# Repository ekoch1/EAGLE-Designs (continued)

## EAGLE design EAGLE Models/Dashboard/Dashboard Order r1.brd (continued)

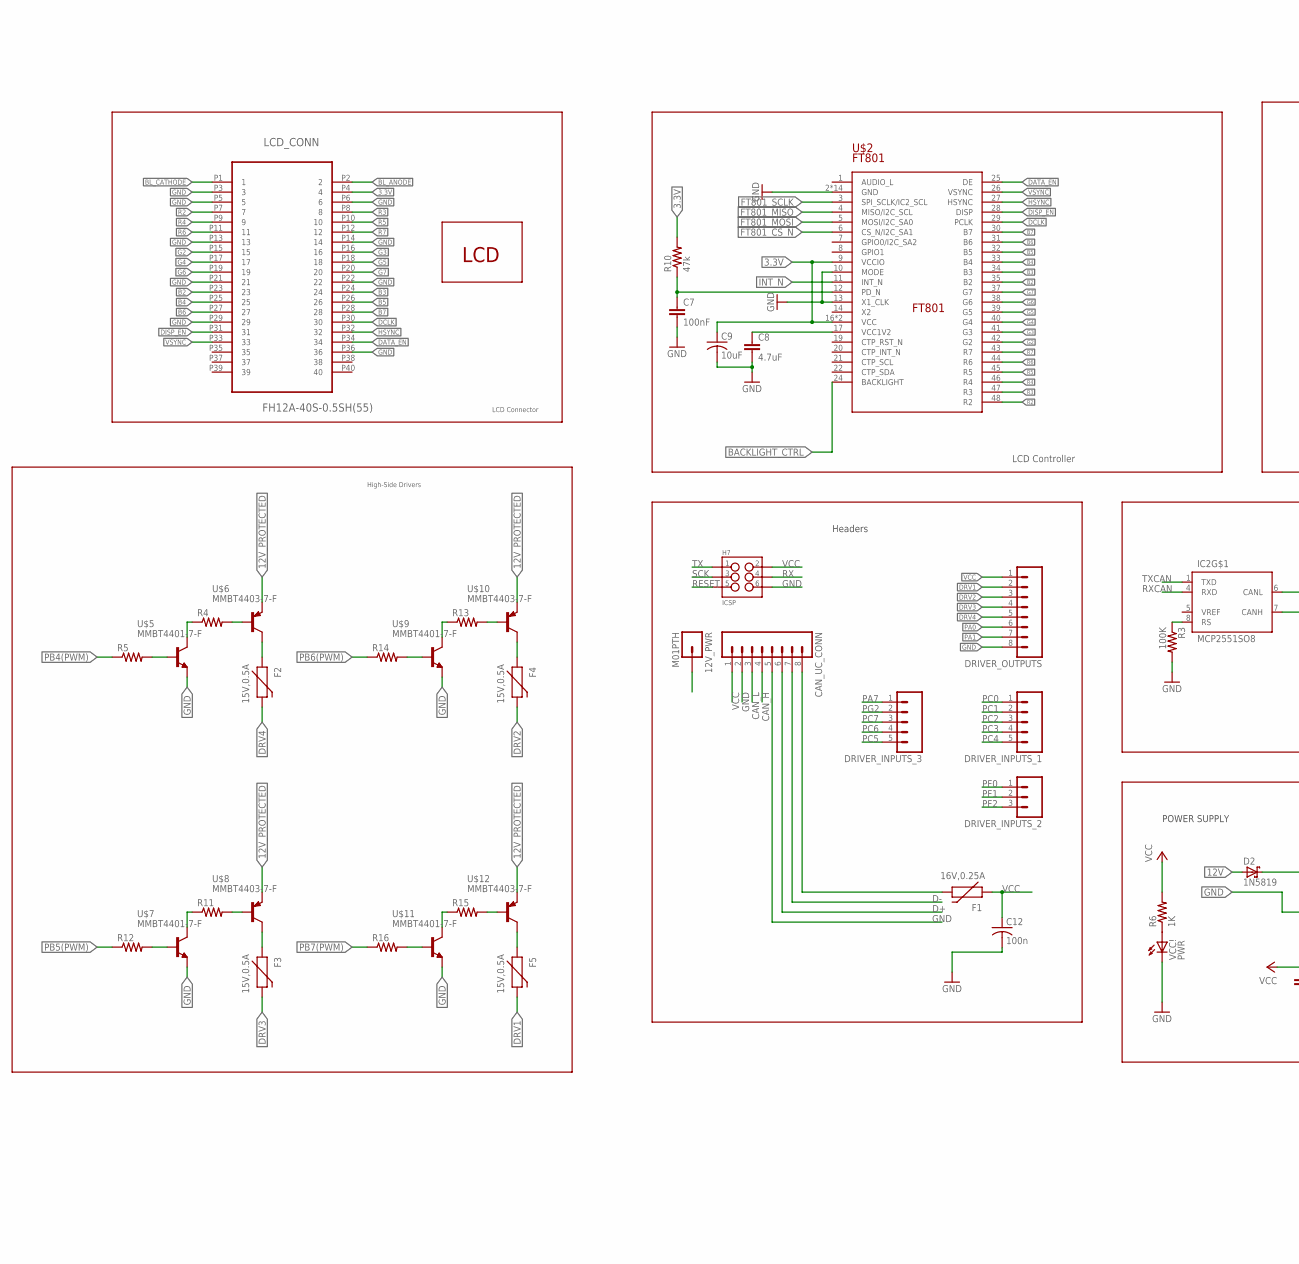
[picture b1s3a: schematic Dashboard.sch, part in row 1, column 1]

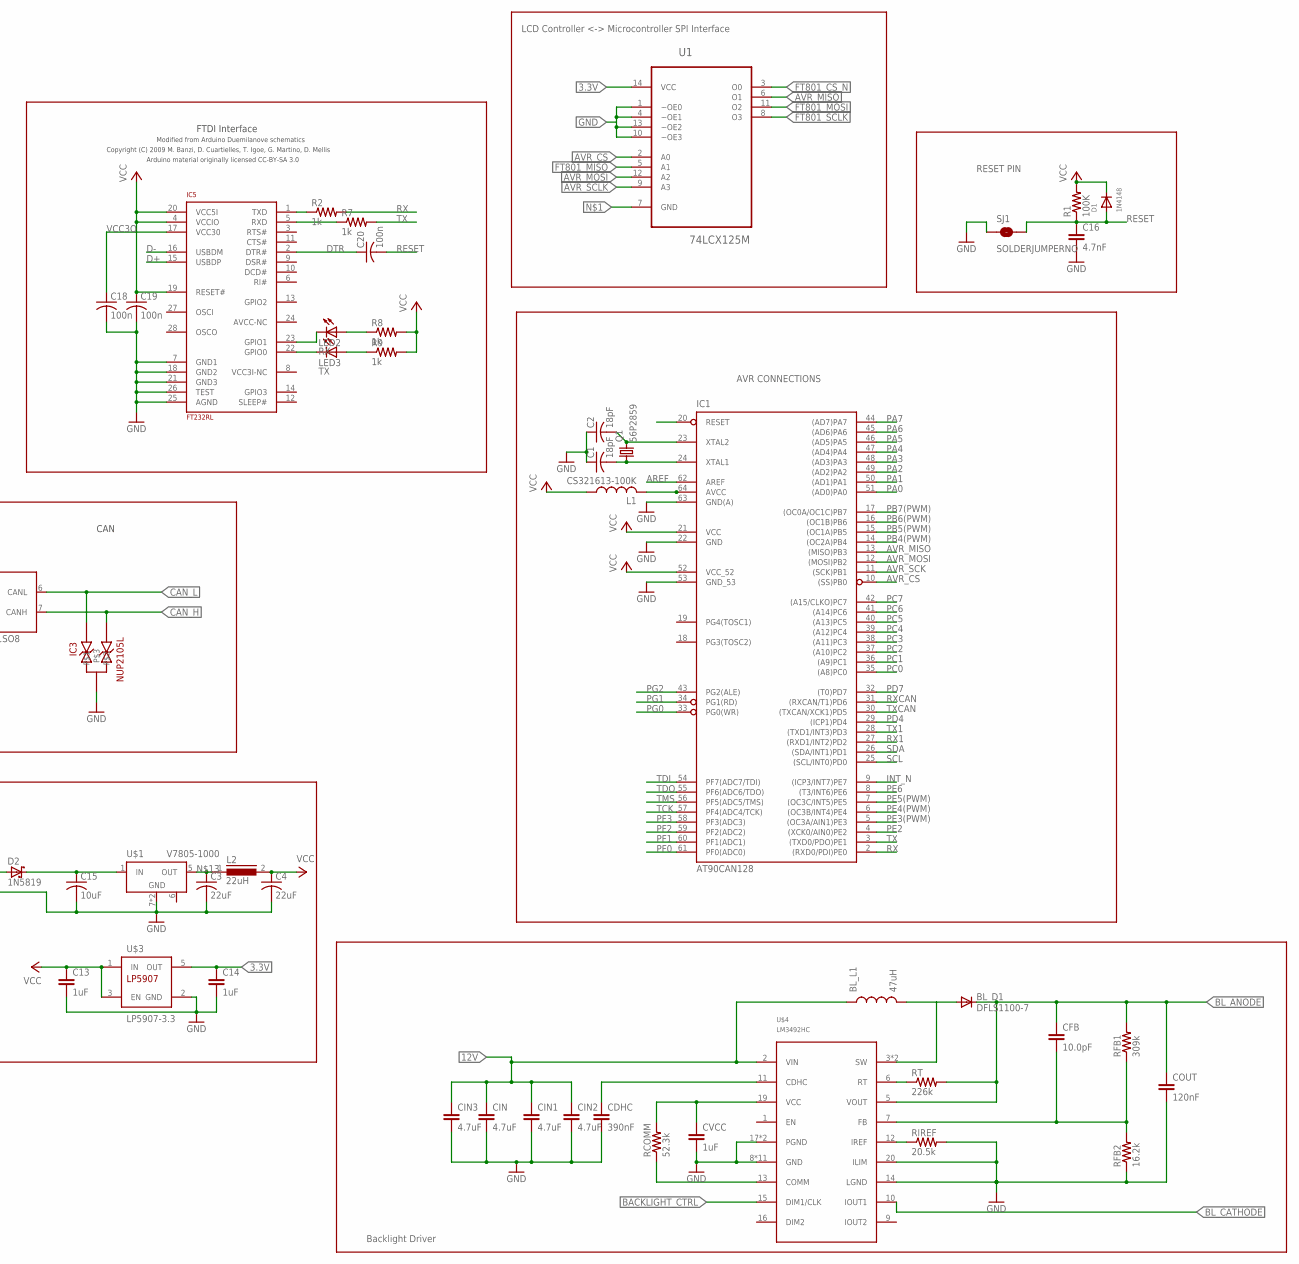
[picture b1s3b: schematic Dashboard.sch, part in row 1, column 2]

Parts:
12V_PWR: M01PTH; 1X01
BL_D1: DFLS1100-7; POWERDI-123
BL_L1: 47uH; 2-SMD
C1, C2: 18pF; C0805
C3, C4: 22uF; C2220
C7: 100nF; 0603-CAP
C8: 4.7uF; 0805
C9, C15: 10uF; C2220
C12, C18, C19, C20: 100n; C0805
C13, C14: 1uF; 0603-CAP
C16: 4.7nF; 0805
CAN_UC_CONN: M081X08; 1X08
CDHC: 390nF; 0603-CAP
CFB: 10.0pF; 0603-CAP
CIN, CIN1, CIN2, CIN3: 4.7uF; 0805
COUT: 120nF; 0805
CVCC: 1uF; 0603-CAP
D1: 1N4148; SOD-123
D2: 1N5819; SOD123
DRIVER_INPUTS_1, DRIVER_INPUTS_3: M05PTH; 1X05
DRIVER_INPUTS_2: M03PTH; 1X03
DRIVER_OUTPUTS: M081X08; 1X08
F1: 16V,0.25A; PTC-1206
F2, F3, F4, F5: 15V,0.5A; PTC-1206
H7: ICSP; 2X3_SMD_FCI_54202-G30
IC1: AT90CAN128; TQFP64
IC2: MCP2551SO8; SO08
IC3: NUP2105L; SOT-23
IC5: FT232RL; SSOP28
L1: CS321613-100K; L3216C
L2: 22uH; DR73
LCD_CONN: FH12A-40S-0.5SH(55); HIROSE_FH12A-40S-0.5SH(55)
LED2: RX; CHIPLED_0805
LED3: TX; CHIPLED_0805
Q1: 56P2859; HC49UP
R1, R3: 100K; R0805
R2, R7, R8, R9: 1k; R0805
R4, R5, R11, R12, R13, R14, R15, R16: RESISTOR0603; 0603-RES
R6: 1K; R0805
R10: 47k; 0603-RES
RCOMM: 52.3k; 0603-RES
RFB1: 309k; 0603-RES
RFB2: 16.2k; 0603-RES
RIREF: 20.5k; 0603-RES
RT: 226k; 0603-RES
SJ1: SOLDERJUMPERNO; SJ_2S-NO
U1: 74LCX125M; SOIC127P600X175-14N
U$1: V7805-1000; V78XX-1000
U$2: FT801; RGZ48_5P15X5P15
U$3: LP5907-3.3; SOT23-DBV
U$4: LM3492HC; PWP0020A
U$5, U$7, U$9, U$11: MMBT4401-7-F; SOT-23-3
U$6, U$8, U$10, U$12: MMBT4403-7-F; SOT-23-3
U$13: TCG043WQLBAANN-GN00; TCG043WQLBAANN
VCC!: PWR; CHIPLED_0805

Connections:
3.3V: C9.1, C14.1, LCD_CONN.P4 (4), R10.2, U1.14 (VCC), U$2.9 (VCCIO), U$2.16 (VCC), U$2.18 (VCC), U$3.5 (OUT)
12V: 12V_PWR.1, BL_L1.1, CIN.1, CIN1.1, CIN2.1, CIN3.1, D2.A, U$4.2 (VIN); also elsewhere on the board
12V_PROTECTED: C15.1, D2.C, U$1.1 (IN), U$6.P$3 (E), U$8.P$3 (E), U$10.P$3 (E), U$12.P$3 (E)
AREF: IC1.62 (AREF)
AVR_CS: IC1.10 ((SS)PB0), U1.2 (A0)
AVR_MISO: IC1.13 ((MISO)PB3), U1.6 (O1)
AVR_MOSI: IC1.12 ((MOSI)PB2), U1.12 (A2)
B2: LCD_CONN.P23 (23), U$2.35 (B2)
B3: LCD_CONN.P24 (24), U$2.34 (B3)
B4: LCD_CONN.P25 (25), U$2.33 (B4)
B5: LCD_CONN.P26 (26), U$2.32 (B5)
B6: LCD_CONN.P27 (27), U$2.31 (B6)
B7: LCD_CONN.P28 (28), U$2.30 (B7)
BACKLIGHT_CTRL: U$2.24 (BACKLIGHT), U$4.15 (DIM1/CLK)
BL_ANODE: BL_D1.C, CFB.1, COUT.1, LCD_CONN.P2 (2), RFB1.2, RT.2, U$4.5 (VOUT)
BL_CATHODE: LCD_CONN.P1 (1), U$4.10 (IOUT1)
CAN_H: CAN_UC_CONN.4, IC2.7 (CANH), IC3.2; also elsewhere on the board
CAN_L: CAN_UC_CONN.3, IC2.6 (CANL), IC3.1; also elsewhere on the board
D+: CAN_UC_CONN.6, IC5.15 (USBDP); also elsewhere on the board
D-: CAN_UC_CONN.7, IC5.16 (USBDM); also elsewhere on the board
DATA_EN: LCD_CONN.P34 (34), U$2.25 (DE)
DCLK: LCD_CONN.P30 (30), U$2.29 (PCLK)
DISP_EN: LCD_CONN.P31 (31), U$2.28 (DISP)
DRV1: DRIVER_OUTPUTS.2, F5.2; also elsewhere on the board
DRV2: DRIVER_OUTPUTS.3, F4.2; also elsewhere on the board
DRV3: DRIVER_OUTPUTS.4, F3.2; also elsewhere on the board
DRV4: DRIVER_OUTPUTS.5, F2.2
DTR: C20.1, IC5.2 (DTR#)
FT801_CS_N: U1.3 (O0), U$2.6 (CS_N/I2C_SA1)
FT801_MISO: U1.5 (A1), U$2.4 (MISO/I2C_SCL)
FT801_MOSI: U1.11 (O2), U$2.5 (MOSI/I2C_SA0)
FT801_SCLK: U1.8 (O3), U$2.3 (SPI_SCLK/IC2_SCL)
G2: LCD_CONN.P15 (15), U$2.42 (G2)
G3: LCD_CONN.P16 (16), U$2.41 (G3)
G4: LCD_CONN.P17 (17), U$2.40 (G4)
G5: LCD_CONN.P18 (18), U$2.39 (G5)
G6: LCD_CONN.P19 (19), U$2.38 (G6)
G7: LCD_CONN.P20 (20), U$2.37 (G7)
GND: C1.1, C2.1, C3.2, C4.2, C7.2, C8.2, C9.2, C12.2, C13.2, C14.2, C15.2, C16.2, C18.2, C19.2, CAN_UC_CONN.2, CAN_UC_CONN.5, CDHC.2, CIN.2, CIN1.2, CIN2.2, CIN3.2, COUT.2, CVCC.2, DRIVER_OUTPUTS.8, H7.6, IC1.22 (GND), IC1.53 (GND_53), IC1.63 (GND(A)), IC2.2 (GND), IC3.3, IC5.7 (GND1), IC5.18 (GND2), IC5.21 (GND3), IC5.25 (AGND), IC5.26 (TEST), LCD_CONN.P3 (3), LCD_CONN.P5 (5), LCD_CONN.P6 (6), LCD_CONN.P13 (13), LCD_CONN.P14 (14), LCD_CONN.P21 (21), LCD_CONN.P22 (22), LCD_CONN.P29 (29), LCD_CONN.P36 (36), R3.2, RFB2.1, RIREF.2, SJ1.1, U1.1 (~OE0), U1.4 (~OE1), U1.10 (~OE3), U1.13 (~OE2), U$1.7 (GND), U$1.9 (GND), U$2.2 (GND), U$2.10 (MODE), U$2.13 (X1_CLK), U$2.15 (GND), U$2.23 (GND), U$2.36 (GND), U$2.EP (GND), U$2.V_1 (GND), U$2.V_2 (GND), U$2.V_3 (GND), U$2.V_4 (GND), U$2.V_5 (GND), U$2.V_6 (GND), U$2.V_7 (GND), U$2.V_8 (GND), U$2.V_9 (GND), U$3.2 (GND), U$4.8 (GND), U$4.14 (LGND), U$4.17 (PGND), U$4.18 (PGND), U$4.20 (ILIM), U$4.EP (GND), U$4.P$1 (GND), U$4.P$2 (GND), U$4.P$3 (GND), U$4.P$4 (GND), U$4.P$5 (GND), U$4.P$6 (GND), U$4.P$7 (GND), U$4.P$8 (GND), U$4.P$9 (GND), U$5.P$3 (E), U$7.P$3 (E), U$9.P$3 (E), U$11.P$3 (E), VCC!.C; also elsewhere on the board
HSYNC: LCD_CONN.P32 (32), U$2.27 (HSYNC)
INT_N: IC1.9 ((ICP3/INT7)PE7), U$2.11 (INT_N)
M8RXD: IC5.1 (TXD), R2.1
M8TXD: IC5.5 (RXD), R7.1
unnamed: C8.1, U$2.17 (VCC1V2)
unnamed: C7.1, R10.1, U$2.12 (PD_N)
unnamed: CVCC.1, RCOMM.2, U$4.19 (VCC)
unnamed: RCOMM.1, U$4.13 (COMM)
unnamed: IC2.8 (RS), R3.1
unnamed: CDHC.1, U$4.11 (CDHC)
unnamed: BL_D1.A, BL_L1.2, U$4.3 (SW), U$4.4 (SW)
unnamed: R6.1, VCC!.A
unnamed: CFB.2, RFB1.1, RFB2.2, U$4.7 (FB)
unnamed: C1.2, IC1.24 (XTAL1), Q1.1
unnamed: RT.1, U$4.6 (RT)
unnamed: C3.1, L2.1, U$1.5 (OUT)
unnamed: RIREF.1, U$4.12 (IREF)
unnamed: IC1.64 (AVCC), L1.2
unnamed: R5.2, U$5.P$2 (B)
unnamed: R4.2, U$6.P$2 (B)
unnamed: R4.1, U$5.P$1 (C)
unnamed: F2.1, U$6.P$1 (C)
unnamed: R12.2, U$7.P$2 (B)
unnamed: R11.2, U$8.P$2 (B)
unnamed: R11.1, U$7.P$1 (C)
unnamed: F3.1, U$8.P$1 (C)
unnamed: R14.2, U$9.P$2 (B)
unnamed: IC5.23 (GPIO1), LED2.C
unnamed: R13.2, U$10.P$2 (B)
unnamed: IC5.22 (GPIO0), LED3.C
unnamed: LED2.A, R8.1
unnamed: LED3.A, R9.1
unnamed: R13.1, U$9.P$1 (C)
unnamed: F4.1, U$10.P$1 (C)
unnamed: R16.2, U$11.P$2 (B)
unnamed: R15.2, U$12.P$2 (B)
unnamed: R15.1, U$11.P$1 (C)
unnamed: F5.1, U$12.P$1 (C)
PA0: DRIVER_OUTPUTS.6, IC1.51 ((AD0)PA0)
PA1: DRIVER_OUTPUTS.7, IC1.50 ((AD1)PA1)
PA2: IC1.49 ((AD2)PA2)
PA3: IC1.48 ((AD3)PA3)
PA4: IC1.47 ((AD4)PA4)
PA5: IC1.46 ((AD5)PA5)
PA6: IC1.45 ((AD6)PA6)
PA7: DRIVER_INPUTS_3.1, IC1.44 ((AD7)PA7)
PB4(PWM): IC1.14 ((OC2A)PB4), R5.1
PB5(PWM): IC1.15 ((OC1A)PB5), R12.1
PB6(PWM): IC1.16 ((OC1B)PB6), R14.1
PB7(PWM): IC1.17 ((OC0A/OC1C)PB7), R16.1
PC0: DRIVER_INPUTS_1.1, IC1.35 ((A8)PC0); also elsewhere on the board
PC1: DRIVER_INPUTS_1.2, IC1.36 ((A9)PC1)
PC2: DRIVER_INPUTS_1.3, IC1.37 ((A10)PC2)
PC3: DRIVER_INPUTS_1.4, IC1.38 ((A11)PC3)
PC4: DRIVER_INPUTS_1.5, IC1.39 ((A12)PC4)
PC5: DRIVER_INPUTS_3.5, IC1.40 ((A13)PC5)
PC6: DRIVER_INPUTS_3.4, IC1.41 ((A14)PC6)
PC7: DRIVER_INPUTS_3.3, IC1.42 ((A15/CLKO)PC7)
PD4: IC1.29 ((ICP1)PD4)
PD7: IC1.32 ((T0)PD7)
PE2: IC1.4 ((XCK0/AIN0)PE2)
PE3(PWM): IC1.5 ((OC3A/AIN1)PE3)
PE4(PWM): IC1.6 ((OC3B/INT4)PE4)
PE5(PWM): IC1.7 ((OC3C/INT5)PE5)
PE6: IC1.8 ((T3/INT6)PE6)
PF0: DRIVER_INPUTS_2.1, IC1.61 (PF0(ADC0)); also elsewhere on the board
PF1: DRIVER_INPUTS_2.2, IC1.60 (PF1(ADC1)); also elsewhere on the board
PF2: DRIVER_INPUTS_2.3, IC1.59 (PF2(ADC2)); also elsewhere on the board
PF3: IC1.58 (PF3(ADC3))
PG0: IC1.33 (PG0(WR))
PG1: IC1.34 (PG1(RD))
PG2: DRIVER_INPUTS_3.2, IC1.43 (PG2(ALE))
R2: LCD_CONN.P7 (7), U$2.48 (R2)
R3: LCD_CONN.P8 (8), U$2.47 (R3)
R4: LCD_CONN.P9 (9), U$2.46 (R4)
R5: LCD_CONN.P10 (10), U$2.45 (R5)
R6: LCD_CONN.P11 (11), U$2.44 (R6)
R7: LCD_CONN.P12 (12), U$2.43 (R7)
RESET: C16.1, C20.2, D1.A, H7.5, IC1.20 (RESET), R1.1, SJ1.2
RX: H7.4, IC1.2 ((RXD0/PDI)PE0), R2.2
RX1: IC1.27 ((RXD1/INT2)PD2)
RXCAN: IC1.31 ((RXCAN/T1)PD6), IC2.4 (RXD)
SCK: H7.3
SCL: IC1.25 ((SCL/INT0)PD0)
SDA: IC1.26 ((SDA/INT1)PD1)
TCK: IC1.57 (PF4(ADC4/TCK))
TDI: IC1.54 (PF7(ADC7/TDI))
TDO: IC1.55 (PF6(ADC6/TDO))
TMS: IC1.56 (PF5(ADC5/TMS))
TX: H7.1, IC1.3 ((TXD0/PDO)PE1), R7.2
TX1: IC1.28 ((TXD1/INT3)PD3)
TXCAN: IC1.30 ((TXCAN/XCK1)PD5), IC2.1 (TXD)
USB_V_IN: CAN_UC_CONN.8, F1.2; also elsewhere on the board
VCC: C4.1, C12.1, C13.1, C19.1, CAN_UC_CONN.1, D1.C, DRIVER_OUTPUTS.1, F1.1, H7.2, IC1.21 (VCC), IC1.52 (VCC_52), IC2.3 (VCC), IC5.4 (VCCIO), IC5.19 (RESET#), IC5.20 (VCC5I), L1.1, L2.2, R1.2, R6.2, R8.2, R9.2, U$3.1 (IN), U$3.3 (EN); also elsewhere on the board
VCC3O: C18.1, IC5.17 (VCC30)
VSYNC: LCD_CONN.P33 (33), U$2.26 (VSYNC)
XTAL1: C2.2, IC1.23 (XTAL2), Q1.2

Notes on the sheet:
POWER SUPPLY
CAN
RESET PIN
AVR CONNECTIONS
FTDI Interface
Headers
Modified from Arduino Duemilanove schematics
Copyright (C) 2009 M. Banzi, D. Cuartielles, T. Igoe, G. Martino, D. Mellis
Arduino material originally licensed CC-BY-SA 3.0
LCD Controller
LCD Controller <-> Microcontroller SPI Interface
Backlight Driver
LCD Connector
High-Side Drivers

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
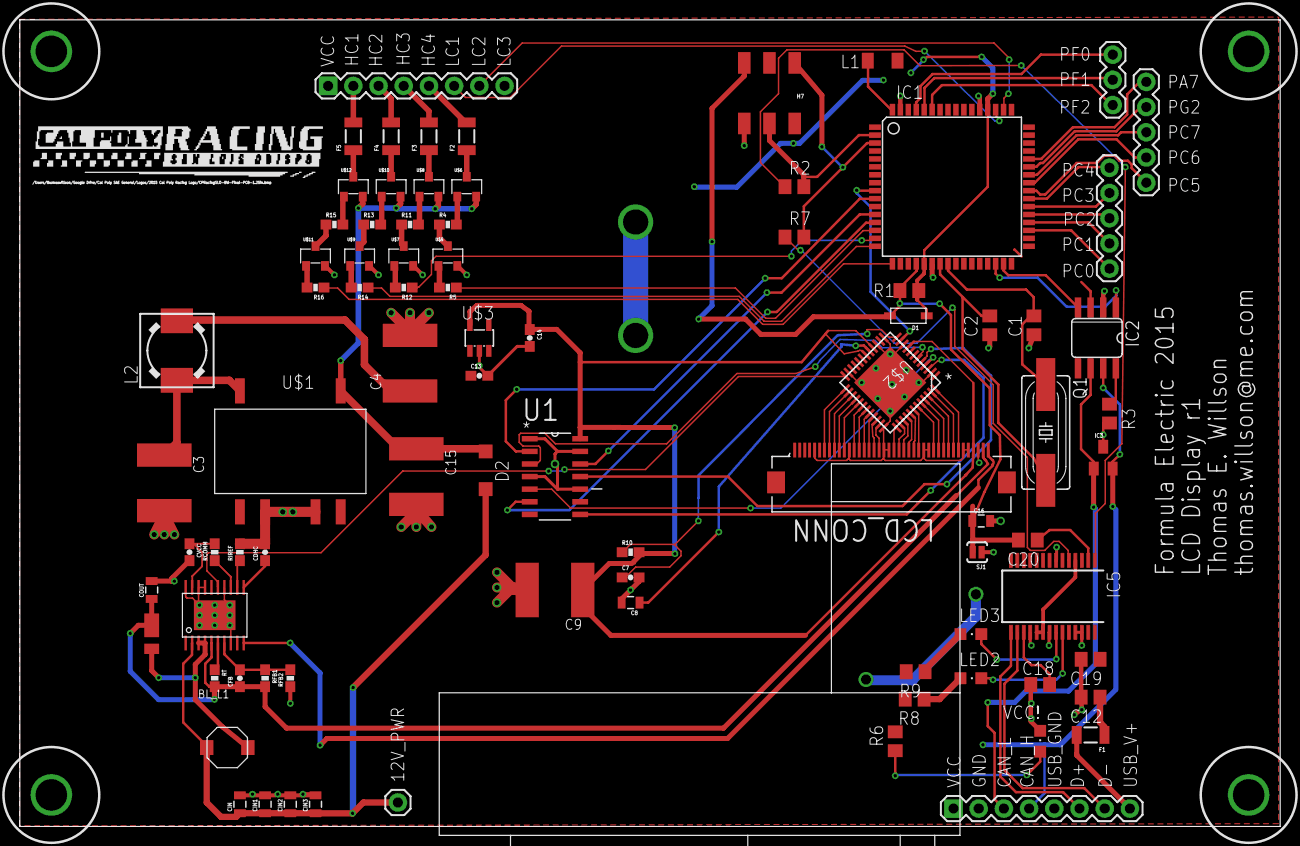
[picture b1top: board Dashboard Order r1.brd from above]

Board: 2 copper layers, 127.0 x 81.3 mm, 86 parts (0 on the bottom side), 111 nets.

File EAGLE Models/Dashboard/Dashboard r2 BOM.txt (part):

Partlist exported from C:/Users/Daniel Baron/Desktop/FSAE2016Boards and Schematics/Dashboard12-12.sch at 1/12/2016 12:52 PM

Part     Value               Device              Package                    Description                                                                         MPN                 OC_FARNELL OC_NEWARK PACKAGE                           SUPPLIER 
BL_D1    DFLS1100-7          DFLS1100-7          POWERDI-123                                                                                                                                                                                        
BL_L1    47uH                LTF4022-D           2-SMD                      LTF4022                                                                                                                                                                 
C1       18pF                C-USC0805           C0805                      CAPACITOR, American symbol                                                                                                                                              
C2       18pF                C-USC0805           C0805                      CAPACITOR, American symbol                                                                                                                                              
C3       22uF                C-USC2220           C2220                      CAPACITOR, American symbol                                                                                                                                              
C4       22uF                C-USC2220           C2220                      CAPACITOR, American symbol                                                                                                                                              
C7       100nF               CAP0603-CAP         0603-CAP                   Capacitor                                                                                                                                                               
C8       4.7uF               CAP0805             0805                       Capacitor                                                                                                                                                               
C9       10uF                C-USC2220           C2220                      CAPACITOR, American symbol                                                                                                                                              
C12      100n                C-USC0805           C0805                      CAPACITOR, American symbol                                                                                                                                              
C13      1uF                 CAP0603-CAP         0603-CAP                   Capacitor                                                                                                                                                               
C14      1uF                 CAP0603-CAP         0603-CAP                   Capacitor                                                                                                                                                               
C15      10uF                C-USC2220           C2220                      CAPACITOR, American symbol                                                                                                                                              
C16      4.7nF               CAP0805             0805                       Capacitor                                                                                                                                                               
C18      100n                C-USC0805           C0805                      CAPACITOR, American symbol                                                                                                                                              
C19      100n                C-USC0805           C0805                      CAPACITOR, American symbol                                                                                                                                              
C20      100n                C-USC0805           C0805                      CAPACITOR, American symbol                                                                                                                                              
CANPWR   MICRO5LOCK          MICRO5LOCK          MICRO5LOCK                                                                                                                                                                                         
CDHC     390nF               CAP0603-CAP         0603-CAP                   Capacitor                                                                                                                                                               
CFB      10.0pF              CAP0603-CAP         0603-CAP                   Capacitor                                                                                                                                                               
CIN      4.7uF               CAP0805             0805                       Capacitor                                                                                                                                                               
CIN1     4.7uF               CAP0805             0805                       Capacitor                                                                                                                                                               
CIN2     4.7uF               CAP0805             0805                       Capacitor                                                                                                                                                               
CIN3     4.7uF               CAP0805             0805                       Capacitor                                                                                                                                                               
COUT     120nF               CAP0805             0805                       Capacitor                                                                                                                                                               
CVCC     1uF                 CAP0603-CAP         0603-CAP                   Capacitor                                                                                                                                                               
D1       1N4148              DIODESOD-123        SOD-123                    Diode                                                                                                                                                                   
D2       1N5819              1N5819-BSOD123      SOD123                     1.0A SCHOTTKY BARRIER RECTIFIER                                                                                                                                         
F1       16V,0.25A           PTCSMD              PTC-1206                   Resettable Fuse PTC                                                                                                                                                     
F2       15V,0.5A            PTCSMD              PTC-1206                   Resettable Fuse PTC                                                                                                                                                     
F3       15V,0.5A            PTCSMD              PTC-1206                   Resettable Fuse PTC                                                                                                                                                     
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
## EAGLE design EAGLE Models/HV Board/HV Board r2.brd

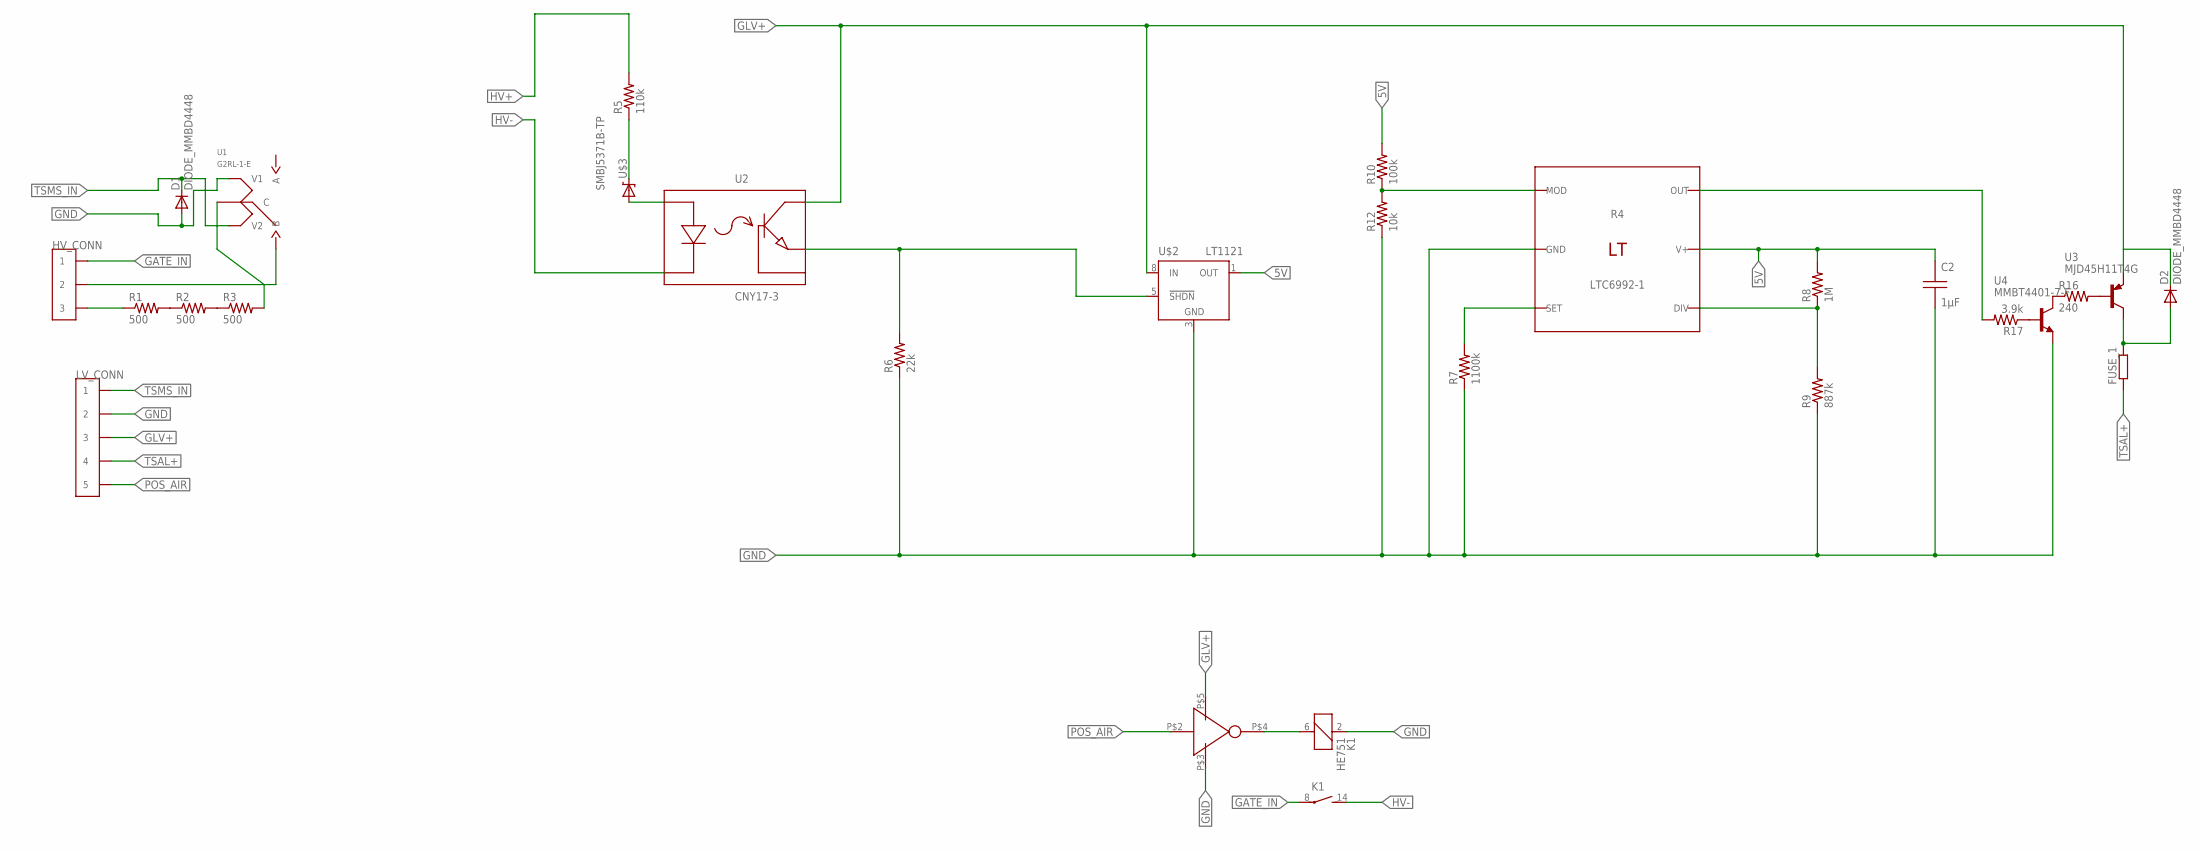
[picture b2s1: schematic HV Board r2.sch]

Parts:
C2: 1µF; C0805
D1, D2: DIODE_MMBD4448; SOT-23-3
FUSE_1: R-EU_R0402; R0402
HV_CONN: CONN_3; CONNECTOR_3
K1: HE751
LV_CONN: CONN_5; CONNECTOR_5
R1, R2, R3: 500; VISHAY_FS20W_RES
R4: LTC6992-1
R5: 110k; AXIAL-0.6
R6: 22k; 0603-RES
R7: 1100k; 0603-RES
R8: 1M; 0603-RES
R9: 887k; 0603-RES
R10: 100k; 0603-RES
R12: 10k; 0603-RES
R16: 240; AXIAL-0.6
R17: 3.9k; R0402
U1: G2RL-1-E; G2RL-1-E_RELAY
U2: CNY17-3
U3: MJD45H11T4G; D-PAK_TO252AA
U4: MMBT4401-7-F; SOT-23-3
U$1: TC4S69F(TE85L,F); SSOP5-P-0.95
U$2: LT1121; SOIC8
U$3: SMBJ5371B-TP; SMB-DIODE

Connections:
5V: C2.1 (A), R4.P$5 (V+), R8.2, R10.2, U$2.1 (OUT)
GATE_IN: HV_CONN.1, HV_CONN.2 (1), K1.8
GLV+: D2.P$1 (C), LV_CONN.5 (3), LV_CONN.6 (3), U2.P$5 (C), U3.3 (E), U$1.P$5 (VCC), U$2.8 (IN)
GND: C2.2 (B), D1.P$2 (A), K1.2 (1), LV_CONN.3 (2), LV_CONN.4 (2), R4.P$2 (GND), R6.1, R7.1, R9.1, R12.1, U1.P$1 (V1), U4.P$3 (E), U$1.P$3 (GND), U$2.3 (GND)
HV+: HV_CONN.3 (2), HV_CONN.4 (2), R5.P$2 (2), U1.P$2 (B), U1.P$7 (B)
HV-: HV_CONN.5 (3), HV_CONN.6 (3), K1.14 (S), R1.P$1 (1), U2.P$1 (K)
unnamed: R5.P$1 (1), U$3.C
unnamed: K1.6 (2), U$1.P$4 (OUT)
unnamed: R3.P$2 (2), U1.P$3 (C), U1.P$6 (C)
unnamed: R1.P$2 (2), R2.P$1 (1)
unnamed: R2.P$2 (2), R3.P$1 (1)
unnamed: R4.P$1 (MOD), R10.1, R12.2
unnamed: U2.P$2 (A), U$3.A
unnamed: R16.P$2 (2), U3.1 (B)
unnamed: R4.P$3 (SET), R7.2
unnamed: R4.P$4 (DIV), R8.1, R9.2
unnamed: R16.P$1 (1), U4.P$1 (C)
unnamed: R17.1, U4.P$2 (B)
unnamed: R4.P$6 (OUT), R17.2
unnamed: R6.2, U2.P$4 (E), U$2.5 (!SHDN)
unnamed: D2.P$2 (A), FUSE_1.2, U3.4 (C)
POS_AIR: LV_CONN.9 (5), LV_CONN.10 (5), U$1.P$2 (IN)
TSAL+: FUSE_1.1, LV_CONN.7 (4), LV_CONN.8 (4)
TSMS_IN: D1.P$1 (C), LV_CONN.1, LV_CONN.2 (1), U1.P$8 (V2)

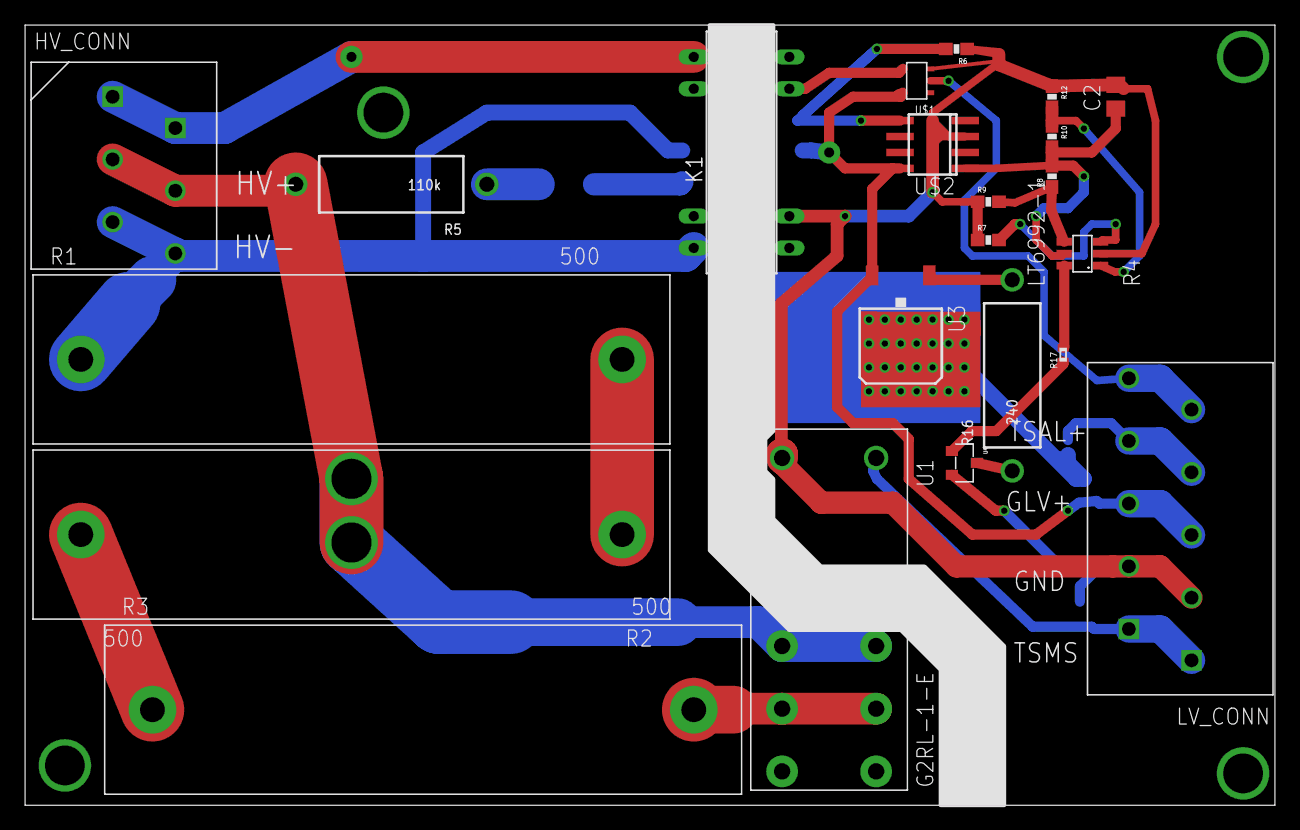
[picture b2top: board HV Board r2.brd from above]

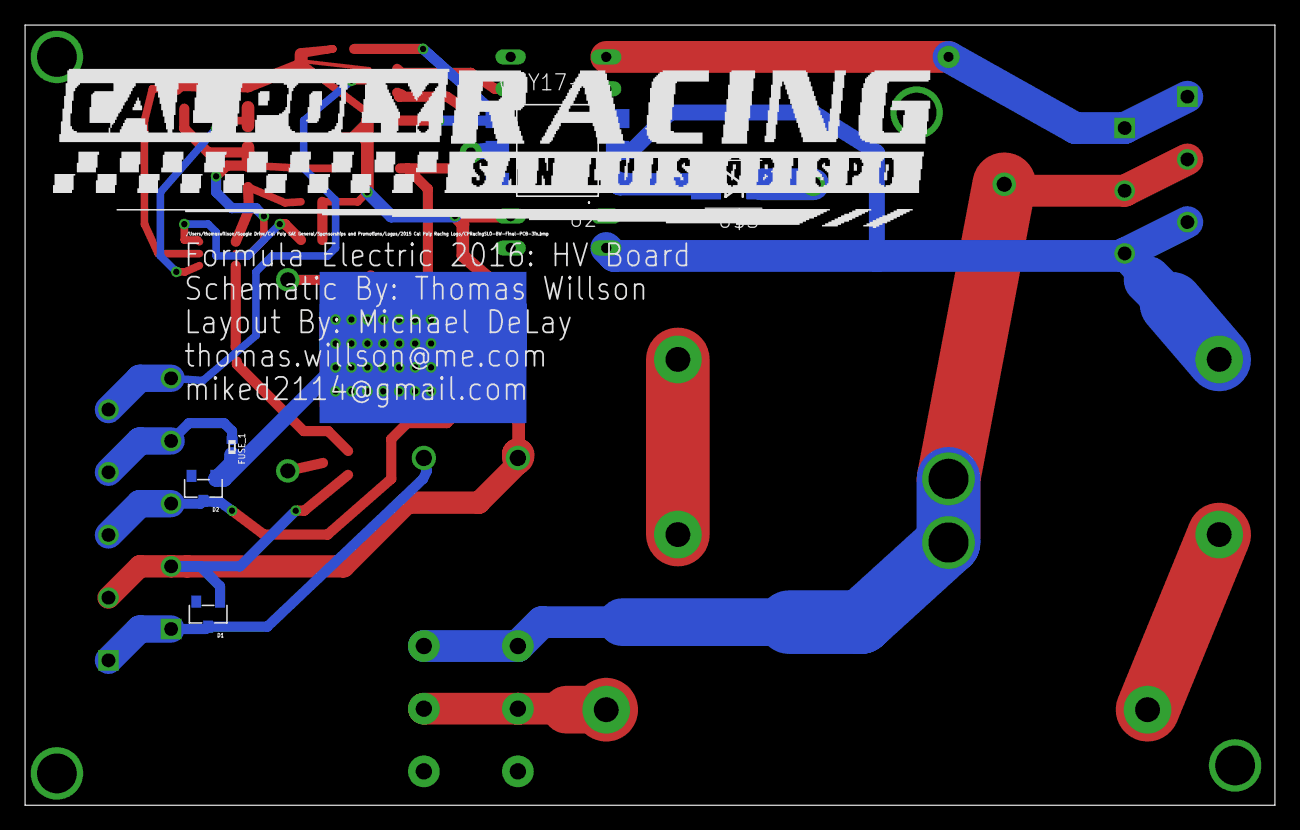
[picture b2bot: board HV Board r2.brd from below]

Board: 2 copper layers, 99.7 x 62.2 mm, 27 parts (5 on the bottom side), 24 nets.

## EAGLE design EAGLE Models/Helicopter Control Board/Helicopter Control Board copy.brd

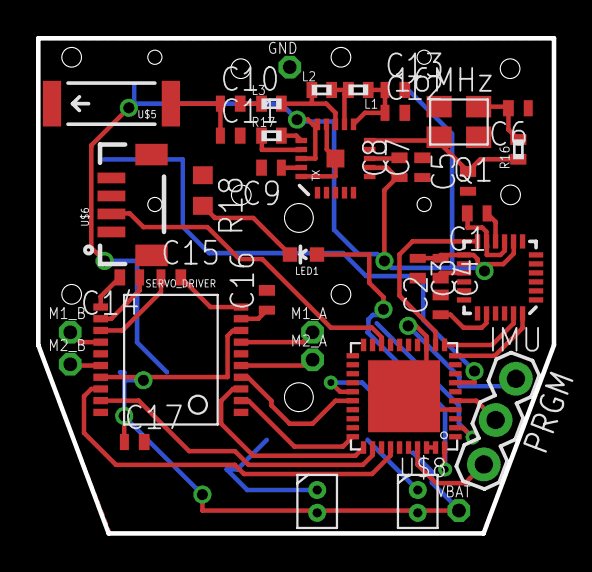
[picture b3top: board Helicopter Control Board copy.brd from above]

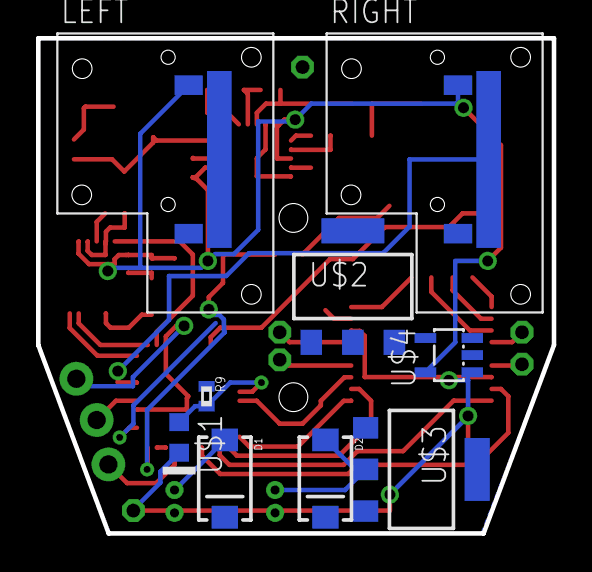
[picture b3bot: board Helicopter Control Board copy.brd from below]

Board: 2 copper layers, 28.7 x 27.5 mm, 49 parts (9 on the bottom side), 47 nets.

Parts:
C1, C3, C14, C15, C16, C17: .1uF; C0402
C2, C12: 2.2nF; C0402
C4, C8: 10nF; C0402
C5, C6: 22pF; C0402
C7: 1nF; C0402
C9: 33nF; C0402
C10: 1.5pF; C0402
C11: 1pF; C0402
C13: 4.7pF; C0402
D1, D2: SMA-DIODE
GND: LSP10
IMU: QFN-24-NP
L1: 2.7nH; R0402
L2: 8.2nH; R0402
L3: 3.9nH; R0402
LED1: LED-0603
LEFT: SURF_POT
M1_A, M1_B, M2_A, M2_B: LSP10
MTR0, MTR1: MOTOR_CONN
PRGM: 1X03_LOCK
Q1: 16MHz; TXC-4SMD
R9: R0402
R16: 1M; R0402
R17: 22k; R0402
R18: 50; R0603
RIGHT: SURF_POT
SERVO_DRIVER: MPC17531A; SSOP_20
TX: NRF24L01SMD; QFN20
U$1: ZENER_0603
U$2, U$3: BSP75N; PG-SOT-223
U$4: LP5907_2.8V; SOT23-DBV
U$5: ANTENNA2SMD5; ANTENNA-CHIP5
U$6: JST_4_VERTICAL; JST-4-SMD-VERT-1.0MM
U$8: G2955IRHA40R; RHA40
VBAT: LSP10

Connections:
A6: R9.2, U$1.A, U$8.25
BODY_LED: U$6.2, U$8.18
B_MTR0: U$3.1, U$8.16
B_MTR1: U$2.1, U$8.17
GND: C1.2, C2.2, C3.2, C4.2, C5.1, C6.1, C7.2, C8.2, C9.2, C11.2, C12.2, C13.2, C16.2, C17.2, GND.MP, IMU.1, IMU.9, IMU.11, IMU.15, IMU.17, IMU.18, LEFT.LO, PRGM.1, Q1.P2, Q1.P4, R9.1, R17.1, R18.1, RIGHT.LO, SERVO_DRIVER.6, SERVO_DRIVER.15, SERVO_DRIVER.20, TX.0, TX.8, TX.14, TX.17, TX.20, U$2.3, U$2.4, U$3.3, U$3.4, U$4.2, U$4.3, U$6.3, U$6.4, U$8.1, U$8.4, U$8.13, U$8.TP
LEFT_POT_OUT: LEFT.OUT, U$8.6
M1_CTRLA: SERVO_DRIVER.2, U$8.30
M1_CTRLB: SERVO_DRIVER.3, U$8.31
M2_CTRLA: SERVO_DRIVER.19, U$8.32
M2_CTRLB: SERVO_DRIVER.18, U$8.34
unnamed: M1_A.MP, SERVO_DRIVER.7
unnamed: M1_B.MP, SERVO_DRIVER.14
unnamed: TX.3, U$8.9
unnamed: TX.4, U$8.23
unnamed: TX.5, U$8.24
unnamed: M2_A.MP, SERVO_DRIVER.5
unnamed: IMU.12, U$8.12
unnamed: IMU.23, U$8.11
unnamed: C1.1, IMU.10
unnamed: C2.1, IMU.20
unnamed: M2_B.MP, SERVO_DRIVER.16
unnamed: C14.1, SERVO_DRIVER.12
unnamed: C14.2, SERVO_DRIVER.11
unnamed: C15.1, SERVO_DRIVER.13
unnamed: C10.2, L3.1
unnamed: D1.A, MTR1.P$1, U$2.2
unnamed: D2.A, MTR0.P$1, U$3.2
unnamed: IMU.24, U$8.10
unnamed: C6.2, Q1.P1, R16.2
unnamed: C5.2, Q1.P3, R16.1, TX.10
unnamed: C9.1, TX.19
unnamed: R17.2, TX.16
unnamed: L1.2, L2.2, TX.12
unnamed: C12.1, C13.1, L1.1, TX.11
unnamed: L2.1, L3.2, TX.13
unnamed: C10.1, C11.1, U$5.FEED
unnamed: TX.2, U$8.2
unnamed: C15.2, SERVO_DRIVER.10
unnamed: LED1.A, U$8.40
unnamed: LED1.C, R18.2
unnamed: C16.1, SERVO_DRIVER.9
PSAVE: SERVO_DRIVER.4, U$8.26
RIGHT_POT_OUT: RIGHT.OUT, U$8.7
RST: PRGM.2, U$8.5
TEST: PRGM.3, U$8.37
VBAT: C17.1, D1.C, D2.C, MTR0.P$2, MTR1.P$2, SERVO_DRIVER.8, SERVO_DRIVER.17, U$1.C, U$4.1, VBAT.MP
VCC: C3.1, C4.1, C7.1, C8.1, IMU.3, IMU.8, IMU.13, LEFT.HI, RIGHT.HI, SERVO_DRIVER.1, TX.7, TX.15, TX.18, U$4.5, U$8.14, U$8.38, U$8.39
